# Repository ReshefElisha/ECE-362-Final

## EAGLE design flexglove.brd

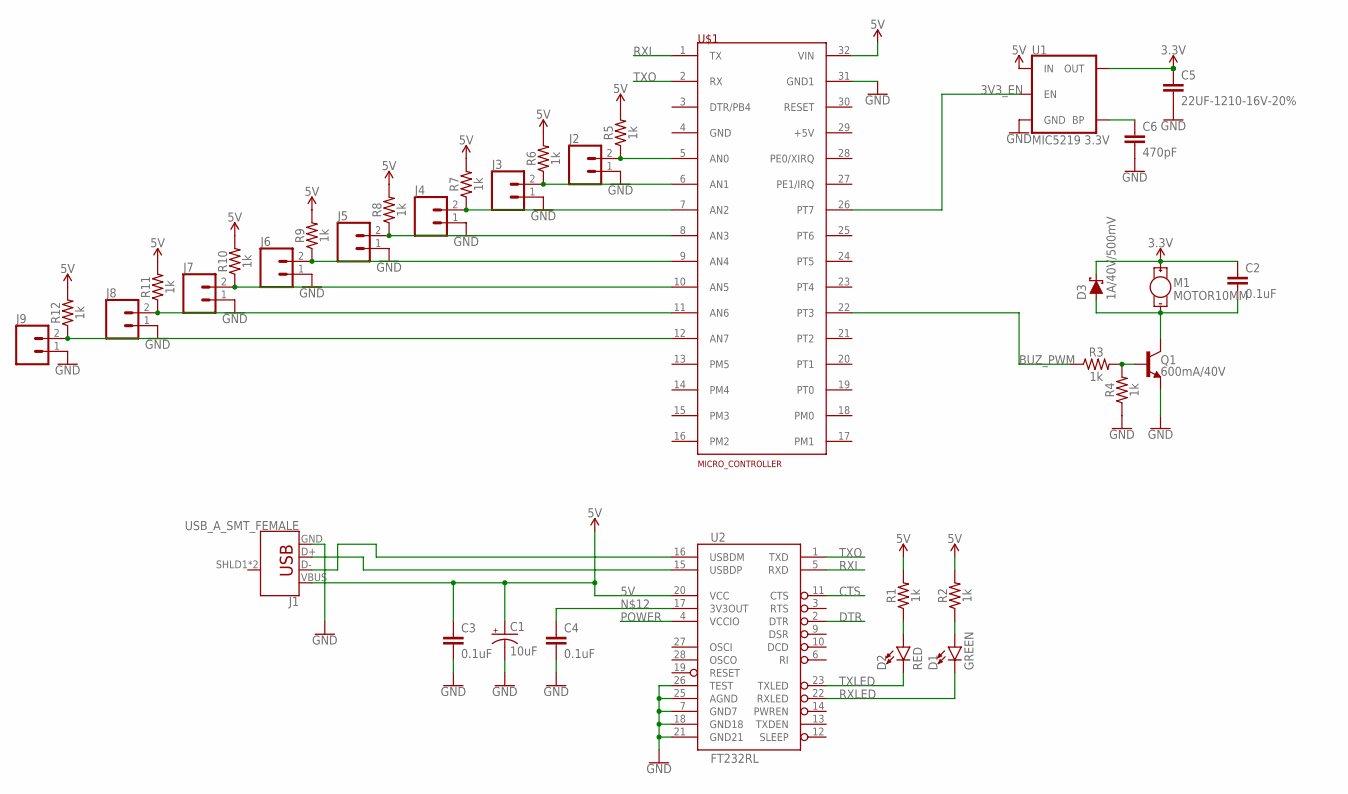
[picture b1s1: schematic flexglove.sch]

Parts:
C1: 10uF; EIA3216
C2, C3, C4: 0.1uF; 0603
C5: 22UF-1210-16V-20%; 1210
C6: 470pF; 0603
D1: GREEN; LED-0603
D2: RED; LED-0603
D3: 1A/40V/500mV; SMA-DIODE
J1: USB_A_SMT_FEMALE; USB-A-S-SILK-FEMALE
J2, J3, J4, J5, J6, J7, J8, J9: CONN_02; 1X02
M1: MOTOR10MM; VIBE-MOTOR-10MM
Q1: 600mA/40V; SOT23-3
R1, R2, R3, R4, R5, R6, R7, R8, R9, R10, R11, R12: 1k; 0603
U1: MIC5219 3.3V; SOT23-5
U2: FT232RL; SSOP28DB
U$1: MICRO_CONTROLLER

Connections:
3.3V: C2.1, C5.1, D3.C, M1.+, U1.5 (OUT)
3V3_EN: U1.3 (EN), U$1.26 (PT7)
5V: C1.+, C3.1, J1.VBUS, R1.2, R2.2, R5.2, R6.2, R7.2, R8.2, R9.2, R10.2, R11.2, R12.2, U1.1 (IN), U2.20 (VCC), U$1.32 (VIN)
BUZ_PWM: R3.1, U$1.22 (PT3)
CTS: U2.11 (CTS)
DTR: U2.2 (DTR)
GND: C1.-, C3.2, C4.2, C5.2, C6.2, J1.GND, J2.1, J3.1, J4.1, J5.1, J6.1, J7.1, J8.1, J9.1, Q1.2 (E), R4.1, U1.2 (GND), U2.7 (GND7), U2.18 (GND18), U2.21 (GND21), U2.25 (AGND), U2.26 (TEST), U$1.31 (GND1)
unnamed: D2.A, R1.1
unnamed: D1.A, R2.1
unnamed: J2.2, R5.1, U$1.5 (AN0)
unnamed: J3.2, R6.1, U$1.6 (AN1)
unnamed: J5.2, R8.1, U$1.8 (AN3)
unnamed: J6.2, R9.1, U$1.9 (AN4)
unnamed: J7.2, R10.1, U$1.10 (AN5)
unnamed: J4.2, R7.1, U$1.7 (AN2)
unnamed: J8.2, R11.1, U$1.11 (AN6)
unnamed: J9.2, R12.1, U$1.12 (AN7)
unnamed: Q1.1 (B), R3.2, R4.2
unnamed: C4.1, U2.17 (3V3OUT)
unnamed: C2.2, D3.A, M1.-, Q1.3 (C)
unnamed: C6.1, U1.4 (BP)
POWER: U2.4 (VCCIO)
RXI: U2.5 (RXD), U$1.1 (TX)
RXLED: D1.C, U2.22 (RXLED)
TXLED: D2.C, U2.23 (TXLED)
TXO: U2.1 (TXD), U$1.2 (RX)
USB_D+: J1.D+, U2.15 (USBDP)
USB_D-: J1.D-, U2.16 (USBDM)

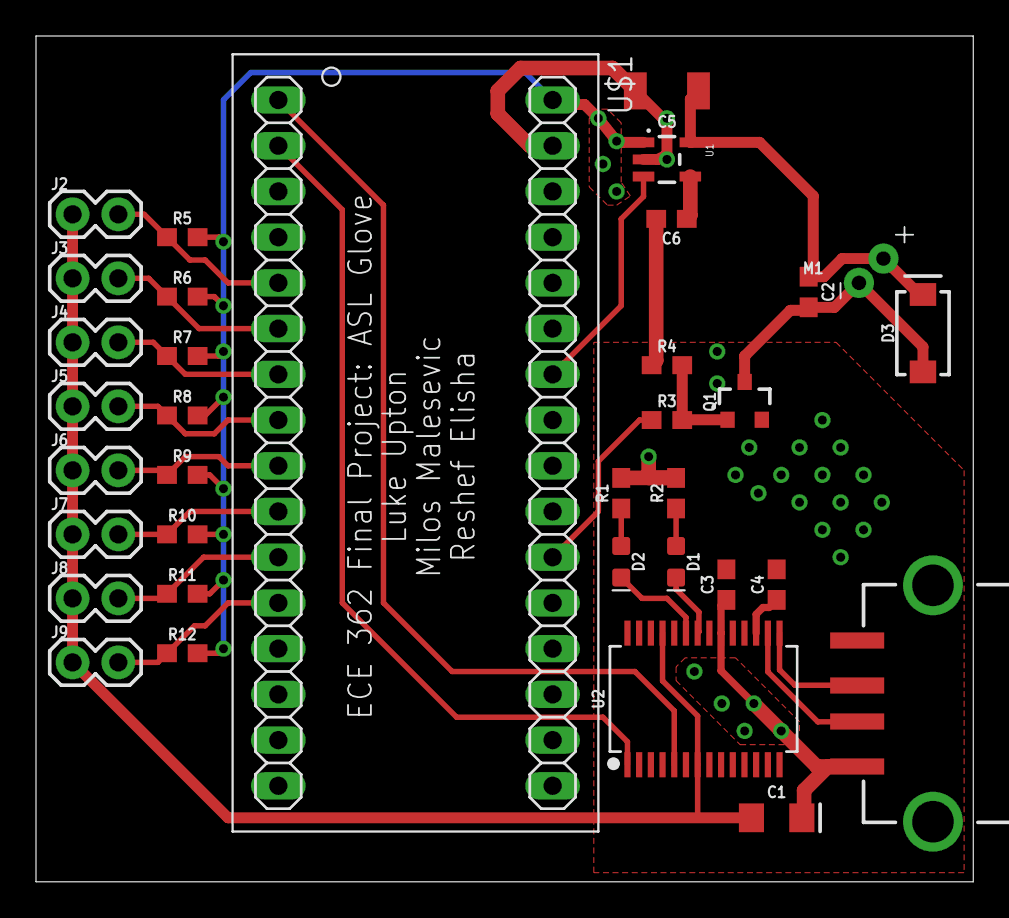
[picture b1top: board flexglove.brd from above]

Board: 2 copper layers, 52.1 x 47.0 mm, 35 parts (0 on the bottom side), 25 nets.

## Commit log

2017-04-12 Libraries
2017-04-21 parts

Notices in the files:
parts and their libraries:
SparkFun-Capacitors: Licensing: Creative Commons ShareAlike 4.0 International - https://creativecommons.org/licenses/by-sa/4.0
